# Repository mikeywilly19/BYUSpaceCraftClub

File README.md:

# BYUSpaceCraftClub

Files for PocketQube project

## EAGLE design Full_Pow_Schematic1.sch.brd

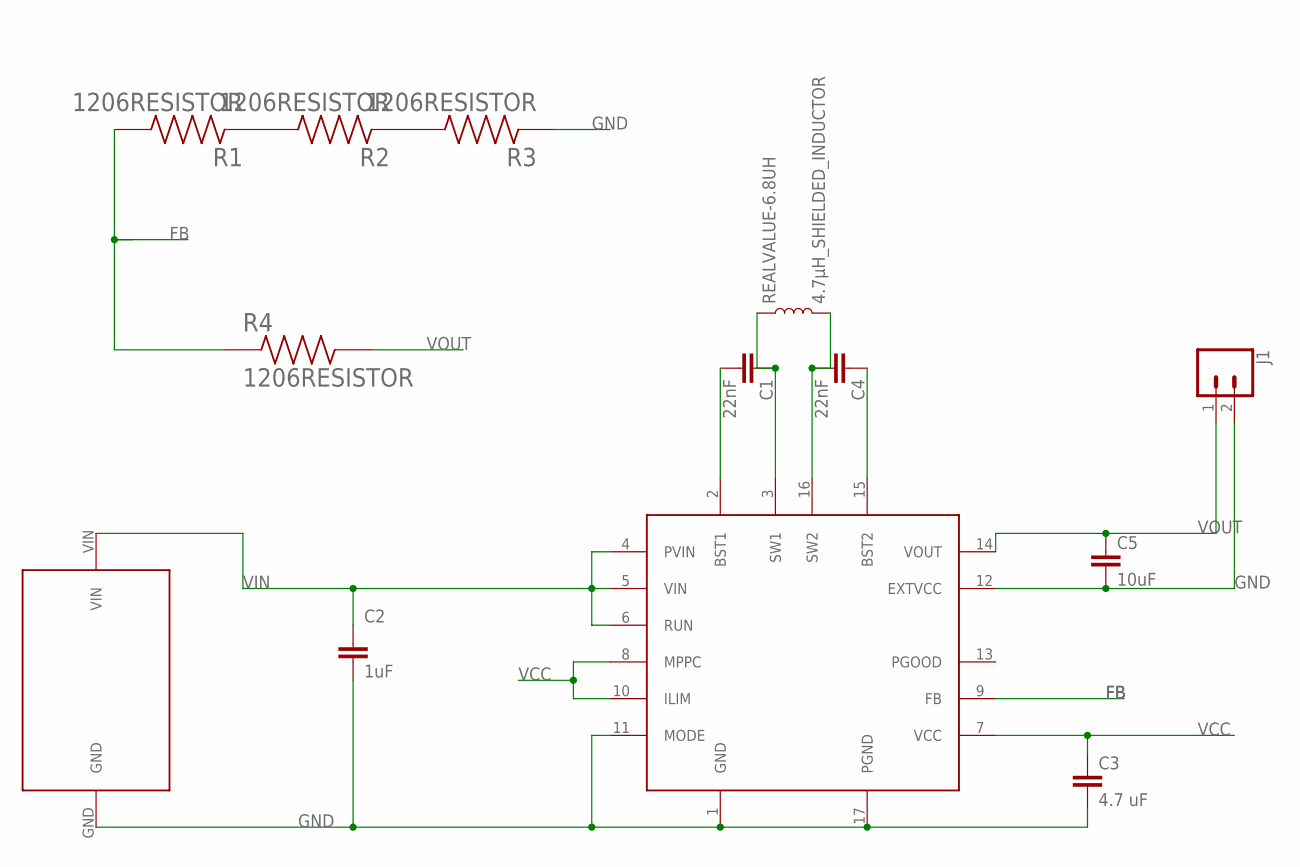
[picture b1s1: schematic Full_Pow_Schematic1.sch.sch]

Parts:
C1, C4: 22nF; 0402
C2: 1uF; 0402
C3: 4.7 uF; 0402
C5: 10uF; 0402
J1: CONN_02; 1X02
R1, R2, R3, R4: 1206RESISTOR; RESC3116X65N
REALVALUE-6.8UH: 4.7μH_SHIELDED_INDUCTOR; 1008(2520)
U$1: LTC3130; SOP50P490X110-17N
U$2: SM101K12L

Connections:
BST1: C1.2, U$1.2 (BST1)
BST2: C4.1, U$1.15 (BST2)
FB: R1.2, R4.1, U$1.9 (FB)
GND: C2.2, C3.2, C5.2, J1.2, R3.1, U$1.1 (GND), U$1.11 (MODE), U$1.12 (EXTVCC), U$1.17 (PGND), U$2.GND
unnamed: R1.1, R2.2
unnamed: R2.1, R3.2
SW1: C1.1, REALVALUE-6.8UH.1, U$1.3 (SW1)
SW2: C4.2, REALVALUE-6.8UH.2, U$1.16 (SW2)
VCC: C3.1, U$1.7 (VCC), U$1.8 (MPPC), U$1.10 (ILIM)
VIN: C2.1, U$1.4 (PVIN), U$1.5 (VIN), U$1.6 (RUN), U$2.VIN
VOUT: C5.1, J1.1, R4.2, U$1.14 (VOUT)

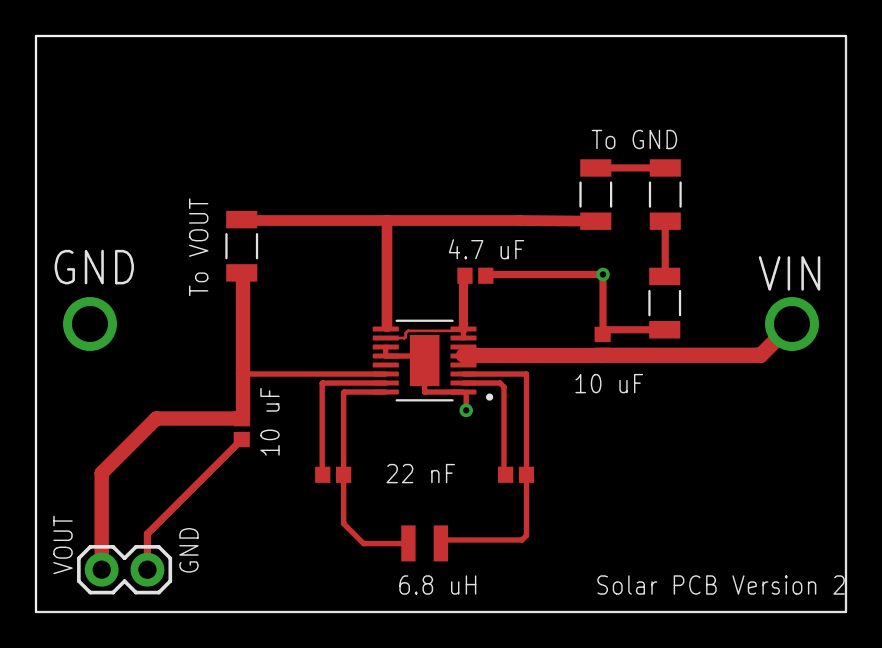
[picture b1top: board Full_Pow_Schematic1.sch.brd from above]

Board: 2 copper layers, 45.0 x 32.0 mm, 13 parts (0 on the bottom side), 11 nets.

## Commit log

2022-09-20 Moved files to new directory
2023-02-17 Edits to power pcb
2023-02-17 Added files for weather ballon test on SAMD21
2023-02-20 ArduCam libraries to WB-test
2023-02-21 added Libraries for Adafruit sensor and IO bus also changed camera test Main.cpp to the full function example code
2023-02-21 Adafruit sensor added to new directory
2023-02-22 Adafruit BME library added
2023-02-22 Adafruit BUS IO
2023-02-23 Edited libraries to fix calling issues
2023-02-23 Added test for SD card reading/writing etc
2023-02-26 Changed pin #'s to match new circuit
2023-03-01 Update test code for new test board
2023-03-01 testing Alitmeter
2023-03-01 Base code is added not sure if it works due to some interaction between the SD card and the camera on spi
2023-03-15 working camera writing to SD card
2023-03-15 minor changes for pin placement
2023-03-20 Added code from camera branch to set up camera and take images
2023-03-22 with '#' will be ignored, and an empty message aborts the commit.
2023-03-22 BME test created
2023-03-29 Added FSM branch
2023-03-29 added stuff to the state machine to improve
2023-04-04 Finished the code for the PCB
2023-04-05 Added code for radio transmission
2023-04-07 Added Radio test file
2023-04-12 added additional documentation
2025-03-19 power pcb

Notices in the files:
parts and their libraries:
SparkFun-Capacitors: Licensing: Creative Commons ShareAlike 4.0 International - https://creativecommons.org/licenses/by-sa/4.0
